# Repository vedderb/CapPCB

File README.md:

# CapPCB  

A capacitor PCB for the VESC  

Some capacitors that work from mouser are:  
647-UPW1J681MHD6  
647-UPW1J471MHD  
667-EEU-FC1J471L  

Read more about the VESC at:  
http://vedder.se/2015/01/vesc-open-source-esc/

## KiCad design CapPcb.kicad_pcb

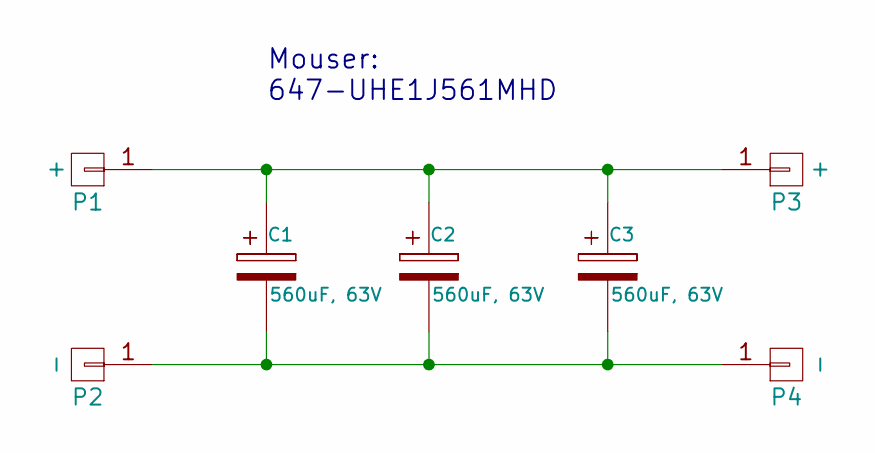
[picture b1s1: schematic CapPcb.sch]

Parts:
C1, C2, C3: 560uF, 63V; C_Radial_D12.5_L25_P5
P1, P3: +; 1pin
P2, P4: -; 1pin

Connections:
unnamed: C1.1, C2.1, C3.1, P1.1, P3.1
unnamed: C1.2, C2.2, C3.2, P2.1, P4.1

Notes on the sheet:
Mouser: 647-UHE1J561MHD

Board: 2 copper layers, 7 parts (0 on the bottom side), 2 nets, no tracks yet.

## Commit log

2015-08-23 Added 3d picture
2015-08-27 Increased drill size
2015-08-27 Added photos and updated README
